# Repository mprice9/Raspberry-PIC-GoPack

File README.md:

# RaspberryPIC GoPack
A Rapsberry Pi powered prototyping platform for wearable robotics and data acquisition.

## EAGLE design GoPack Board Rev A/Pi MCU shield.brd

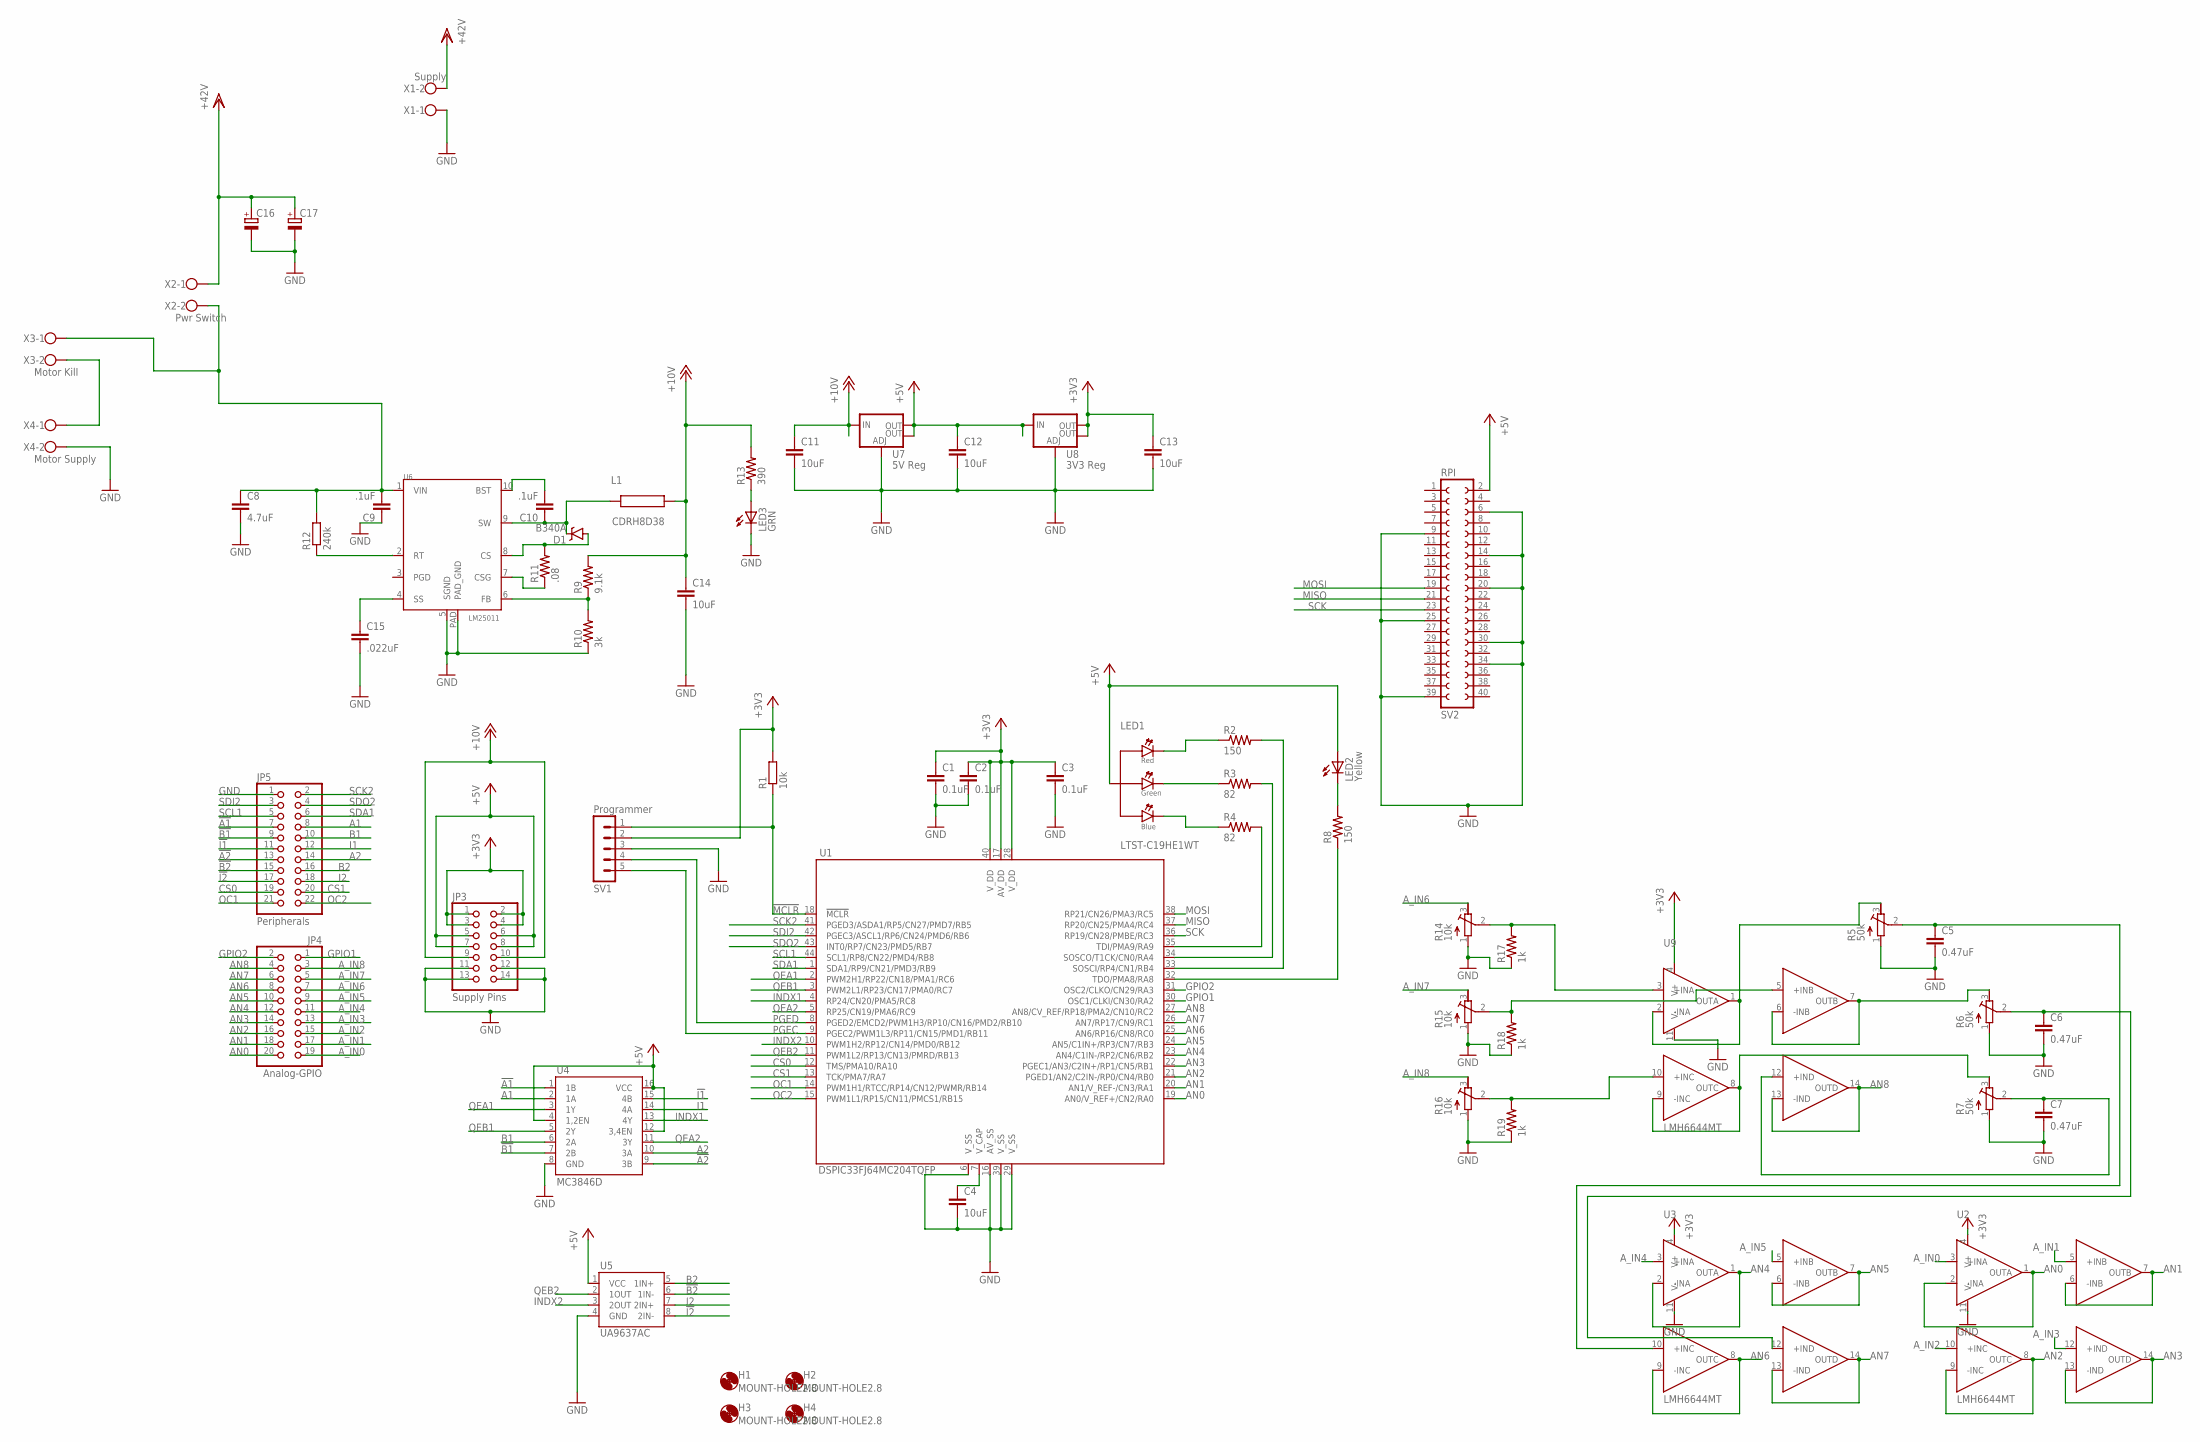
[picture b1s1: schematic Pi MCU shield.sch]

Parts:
C1, C2, C3: 0.1uF; C0603
C4, C14: 10uF; C1206
C5, C6, C7: 0.47uF; C0603
C8: 4.7uF; C1210
C9, C10: .1uF; 0603-CAP
C11, C12, C13: 10uF; C0805
C15: .022uF; 0603-CAP
C16, C17: CPOL-EUE5-13; E5-13
D1: B340A; SMA-DIODE
H1, H2, H3, H4: MOUNT-HOLE2.8; 2,8
JP3: Supply Pins; 2X07
JP4: Analog-GPIO; 2X10
JP5: Peripherals; 2X11
L1: CDRH8D38
LED1: LTST-C19HE1WT; 0606
LED2: Yellow; SML0603
LED3: GRN; CHIP-LED0805
R1: 10k; R0805
R2, R8: 150; R0603
R3, R4: 82; R0603
R5, R6, R7: 50k; RTRIM3224J
R9: 9.1k; 0603-RES
R10: 3k; 0603-RES
R11: .08; 0603-RES
R12: 240k; R0805
R13: 390; 0603-RES
R14, R15, R16: 10k; RTRIM3224J
R17, R18, R19: 1k; R0603
SV1: Programmer; MA05-1
SV2: RPI; FE20-2
U1: DSPIC33FJ64MC204TQFP; TQFP44
U2, U3, U9: LMH6644MT; TSSOP14
U4: MC3846D; SO-16
U5: UA9637AC; SO-08
U6: LM25011; HVSS0P-10
U7: 5V Reg; SOT223
U8: 3V3 Reg; SOT223
X1: Supply; W237-102
X2: Pwr Switch; W237-102
X3: Motor Kill; W237-102
X4: Motor Supply; W237-102

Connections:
!A1: JP5.7, U4.1 (1B)
!A2: JP5.13, U4.9 (3B)
!B1: JP5.9, U4.7 (2B)
!B2: JP5.15, U5.6 (1IN-)
!I1: JP5.11, U4.15 (4B)
!I2: JP5.17, U5.8 (2IN-)
!MCLR: R1.1, SV1.1, U1.18 (!MCLR)
+3V3: C1.1, C2.1, C3.1, C13.1, JP3.1, JP3.2, JP3.3, JP3.4, R1.2, SV1.2, U1.17 (AV_DD), U1.28 (V_DD), U1.40 (V_DD), U2.4 (V+), U3.4 (V+), U8.2 (OUT), U8.4 (OUT), U9.4 (V+)
+5V: C12.1, JP3.5, JP3.6, JP3.7, JP3.8, LED1.4 (ANODE), LED2.A, SV2.2, U4.4 (1,2EN), U4.12 (3,4EN), U4.16 (VCC), U5.1 (VCC), U7.2 (OUT), U7.4 (OUT), U8.3 (IN)
+10V: C11.1, C14.1, JP3.9, JP3.10, L1.P$2 (2), R9.2, R13.2, U7.3 (IN)
A1: JP5.8, U4.2 (1A)
A2: JP5.14, U4.10 (3A)
AN0: JP4.20, U1.19 (AN0/V_REF+/CN2/RA0), U2.1 (OUTA), U2.2 (-INA)
AN1: JP4.18, U1.20 (AN1/V_REF-/CN3/RA1), U2.6 (-INB), U2.7 (OUTB)
AN2: JP4.16, U1.21 (PGED1/AN2/C2IN-/RP0/CN4/RB0), U2.8 (OUTC), U2.9 (-INC)
AN3: JP4.14, U1.22 (PGEC1/AN3/C2IN+/RP1/CN5/RB1), U2.13 (-IND), U2.14 (OUTD)
AN4: JP4.12, U1.23 (AN4/C1IN-/RP2/CN6/RB2), U3.1 (OUTA), U3.2 (-INA)
AN5: JP4.10, U1.24 (AN5/C1IN+/RP3/CN7/RB3), U3.6 (-INB), U3.7 (OUTB)
AN6: JP4.8, U1.25 (AN6/RP16/CN8/RC0), U3.8 (OUTC), U3.9 (-INC)
AN7: JP4.6, U1.26 (AN7/RP17/CN9/RC1), U3.13 (-IND), U3.14 (OUTD)
AN8: JP4.4, U1.27 (AN8/CV_REF/RP18/PMA2/CN10/RC2), U9.13 (-IND), U9.14 (OUTD)
A_IN0: JP4.19, U2.3 (+INA)
A_IN1: JP4.17, U2.5 (+INB)
A_IN2: JP4.15, U2.10 (+INC)
A_IN3: JP4.13, U2.12 (+IND)
A_IN4: JP4.11, U3.3 (+INA)
A_IN5: JP4.9, U3.5 (+INB)
A_IN6: JP4.7, R14.3 (E)
A_IN7: JP4.5, R15.3 (E)
A_IN8: JP4.3, R16.3 (E)
B1: JP5.10, U4.6 (2A)
B2: JP5.16, U5.5 (1IN+)
BLUE: LED1.2 (G_CATHODE), R3.1
CS0: JP5.19, U1.12 (TMS/PMA10/RA10)
CS1: JP5.20, U1.13 (TCK/PMA7/RA7)
GND: C1.2, C2.2, C3.2, C4.2, C5.2, C6.2, C7.2, C8.2, C9.1, C11.2, C12.2, C13.2, C14.2, C15.2, C16.-, C17.-, JP3.11, JP3.12, JP3.13, JP3.14, JP5.1, LED3.C, R5.1 (A), R6.1 (A), R7.1 (A), R10.1, R14.1 (A), R15.1 (A), R16.1 (A), R17.1, R18.1, R19.1, SV1.3, SV2.6, SV2.9, SV2.14, SV2.20, SV2.25, SV2.30, SV2.34, SV2.39, U1.6 (V_SS), U1.16 (AV_SS), U1.29 (V_SS), U1.39 (V_SS), U2.11 (V-), U3.11 (V-), U4.8 (GND), U5.4 (GND), U6.5 (SGND), U6.PAD (PAD_GND), U7.1 (ADJ), U8.1 (ADJ), U9.11 (V-), X1.1, X4.2
GPIO1: JP4.1, U1.30 (OSC1/CLKI/CN30/RA2)
GPIO2: JP4.2, U1.31 (OSC2/CLKO/CN29/RA3)
GREEN: LED1.3 (B_CATHODE), R4.1
I1: JP5.12, U4.14 (4A)
I2: JP5.18, U5.7 (2IN+)
INDX1: U1.4 (RP24/CN20/PMA5/RC8), U4.13 (4Y)
INDX2: U1.10 (PWM1H2/RP12/CN14/PMD0/RB12), U5.3 (2OUT)
MISO: SV2.21, U1.37 (RP20/CN25/PMA4/RC4)
MOSI: SV2.19, U1.38 (RP21/CN26/PMA3/RC5)
unnamed: R15.2 (S), R18.2, U9.5 (+INB)
unnamed: C4.1, U1.7 (V_CAP)
unnamed: C8.1, C9.2, R12.2, U6.1 (VIN), X2.2, X3.1
unnamed: C7.1, R7.2 (S), U9.12 (+IND)
unnamed: C5.1, R5.2 (S), U3.10 (+INC)
unnamed: X3.2, X4.1
unnamed: R14.2 (S), R17.2, U9.3 (+INA)
unnamed: R6.3 (E), U9.6 (-INB), U9.7 (OUTB)
unnamed: R7.3 (E), U9.8 (OUTC), U9.9 (-INC)
unnamed: LED3.A, R13.1
unnamed: LED2.C, R8.2
unnamed: R4.2, U1.35 (TDI/PMA9/RA9)
unnamed: R3.2, U1.34 (SOSCO/T1CK/CN0/RA4)
unnamed: R2.2, U1.33 (SOSCI/RP4/CN1/RB4)
unnamed: R16.2 (S), R19.2, U9.10 (+INC)
unnamed: R8.1, U1.32 (TDO/PMA8/RA8)
unnamed: C10.1, D1.C, L1.P$1 (1), U6.9 (SW)
unnamed: R9.1, R10.2, U6.6 (FB)
unnamed: R12.1, U6.2 (RT)
unnamed: C15.1, U6.4 (SS)
unnamed: D1.A, R11.2, U6.8 (CS)
unnamed: C10.2, U6.10 (BST)
unnamed: R11.1, U6.7 (CSG)
unnamed: R5.3 (E), U9.1 (OUTA), U9.2 (-INA)
unnamed: C6.1, R6.2 (S), U3.12 (+IND)
OC1: JP5.21, U1.14 (PWM1H1/RTCC/RP14/CN12/PWMR/RB14)
OC2: JP5.22, U1.15 (PWM1L1/RP15/CN11/PMCS1/RB15)
PGEC: SV1.5, U1.9 (PGEC2/PWM1L3/RP11/CN15/PMD1/RB11)
PGED: SV1.4, U1.8 (PGED2/EMCD2/PWM1H3/RP10/CN16/PMD2/RB10)
QEA1: U1.2 (PWM2H1/RP22/CN18/PMA1/RC6), U4.3 (1Y)
QEA2: U1.5 (RP25/CN19/PMA6/RC9), U4.11 (3Y)
QEB1: U1.3 (PWM2L1/RP23/CN17/PMA0/RC7), U4.5 (2Y)
QEB2: U1.11 (PWM1L2/RP13/CN13/PMRD/RB13), U5.2 (1OUT)
RED: LED1.1 (R_CATHODE), R2.1
SCK: SV2.23, U1.36 (RP19/CN28/PMBE/RC3)
SCK2: JP5.2, U1.41 (PGED3/ASDA1/RP5/CN27/PMD7/RB5)
SCL1: JP5.5, U1.44 (SCL1/RP8/CN22/PMD4/RB8)
SDA1: JP5.6, U1.1 (SDA1/RP9/CN21/PMD3/RB9)
SDI2: JP5.3, U1.42 (PGEC3/ASCL1/RP6/CN24/PMD6/RB6)
SDO2: JP5.4, U1.43 (INT0/RP7/CN23/PMD5/RB7)
VDD: C16.+, C17.+, X1.2, X2.1

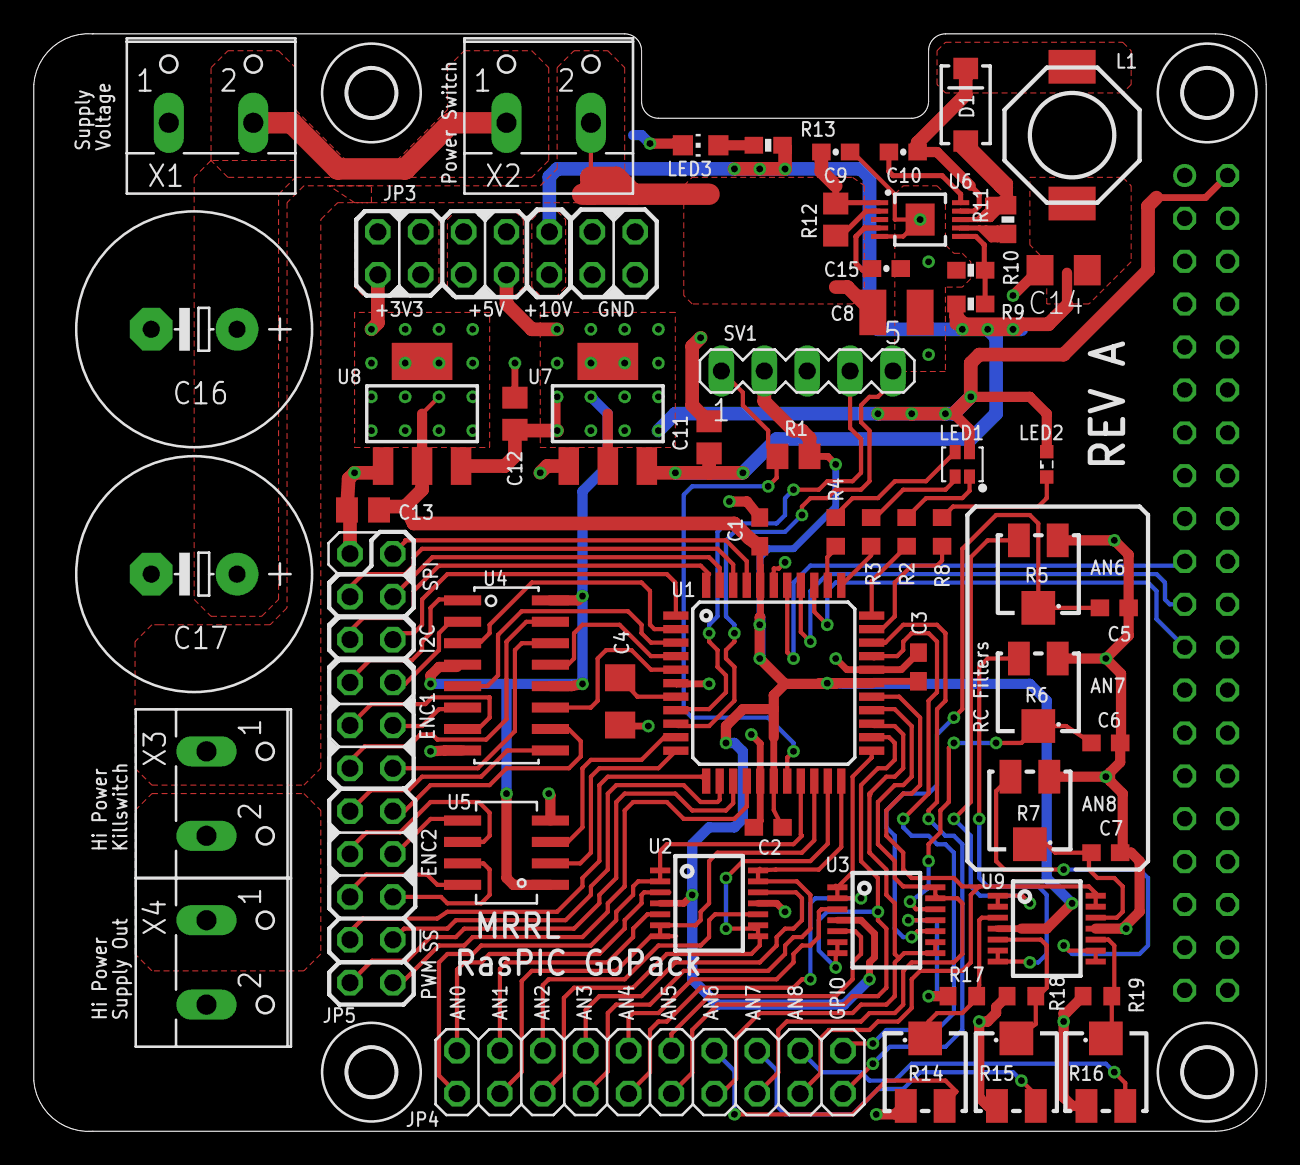
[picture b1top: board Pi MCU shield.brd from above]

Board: 2 copper layers, 73.0 x 65.0 mm, 63 parts (1 on the bottom side), 86 nets.

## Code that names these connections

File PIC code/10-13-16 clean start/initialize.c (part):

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//Initialize Pins
void init_pins(void)
/* Pin Overview Map
//		RA0 - AN0               (PIN19) input
//		RA1 - AN1       		(PIN20) input
//		RA2 - FREE              (PIN30)
//		RA3 - FREE              (PIN31)
//		RA4 - RGB green         (PIN34)
//		RA7 - Chip select 1     (PIN13)
//		RA8 - LED yellow        (PIN32)
//		RA9 - RGB Blue          (PIN35)
//		RA10 - Chip select 0    (PIN12)
//		RB0	- AN2				(PIN21) input
//		RB1	- AN3				(PIN22) input
//		RB2 - AN4               (PIN23) input
//		RB3 - AN5               (PIN24) input      
//		RB4 - RGB Red           (PIN33) 
//		RB5 - SCK2 (SPI2 master)(PIN41)
//		RB6 - SDI2 (SPI2 master)(PIN42) input
//		RB7 - SDO2 (SPI2 master)(PIN43)
//		RB8 - SCL1 (I2C)        (PIN44)
//		RB9 - SDA1 (I2C)        (PIN1)
//		RB10 - Program (PGED2)  (PIN8)
//		RB11 - Program (PGEC2)  (PIN9)
//		RB12 - INDX2 (ENC2)     (PIN10)	input
//		RB13 - QEB2 (ENC2)      (PIN11) input
//		RB14 - OC1   		    (PIN14)
//		RB15 - OC2		        (PIN15)     
//		RC0	- AN6				(PIN25) input
//		RC1	- AN7				(PIN26) input
//		RC2 - AN8               (PIN27) input
//		RC3 - SCK1 (SPI1 slave) (PIN36) input
//		RC4 - SDO1 (SPI1 slave) (PIN37)
//		RC5 - SDI1 (SPI1 slave) (PIN38) input
//		RC6 - QEA1 (ENC1)       (PIN2)  input
//		RC7 - QEB1 (ENC1)       (PIN3)  input
//		RC8 - INDX1 (ENC1)      (PIN4)  input
//		RC9 - QEA2 (ENC2)       (PIN5)  input
*/ 

{
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	LATA = 0x0000;		// all pins set to zero

//    TRISB = 0x3040; 	// 	all analog set to digital out
	TRISB = 0x304F; 	// 	RB0,1,2,3,6,12,13 input,rest PORTB pins set to output
	ODCB = 0x0010;		//	RB4 open drain
	LATB = 0x0000;		//	all pins set to zero
    
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    QEI1CONbits.POSRES = 1;     //Index pulse resets position counter (only applies when QEIM = 4 or 6)
    DFLT1CONbits.IMV = 0;       //A and B input signals both 0 for match on index pulse
    DFLT1CONbits.QEOUT = 0;     //Digital filter outputs are disabled (normal pin operation)
    DFLT1CONbits.QECK = 3;      //1:16 Clock divide for QEA1/QEB1/INDX1
    POS1CNT = 0;
    MAX1CNT = ENC1_RES-1; 
}
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
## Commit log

2017-01-17 Added board files

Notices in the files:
parts and their libraries:
SparkFun-Capacitors: Licensing: Creative Commons ShareAlike 4.0 International - https://creativecommons.org/licenses/by-sa/4.0
